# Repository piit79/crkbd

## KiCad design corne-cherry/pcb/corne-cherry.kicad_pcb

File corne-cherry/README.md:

# Corne Cherry

This version is for standard Cherry MX-compatible switches. It has specific PCBs for left and right half.

The following modifications have been made by 42. Keebs:

* Add power switch and battery contacts
* Add back the possibility to break off the 6th column
* Remove the PCB panel frame to save material/reduce waste

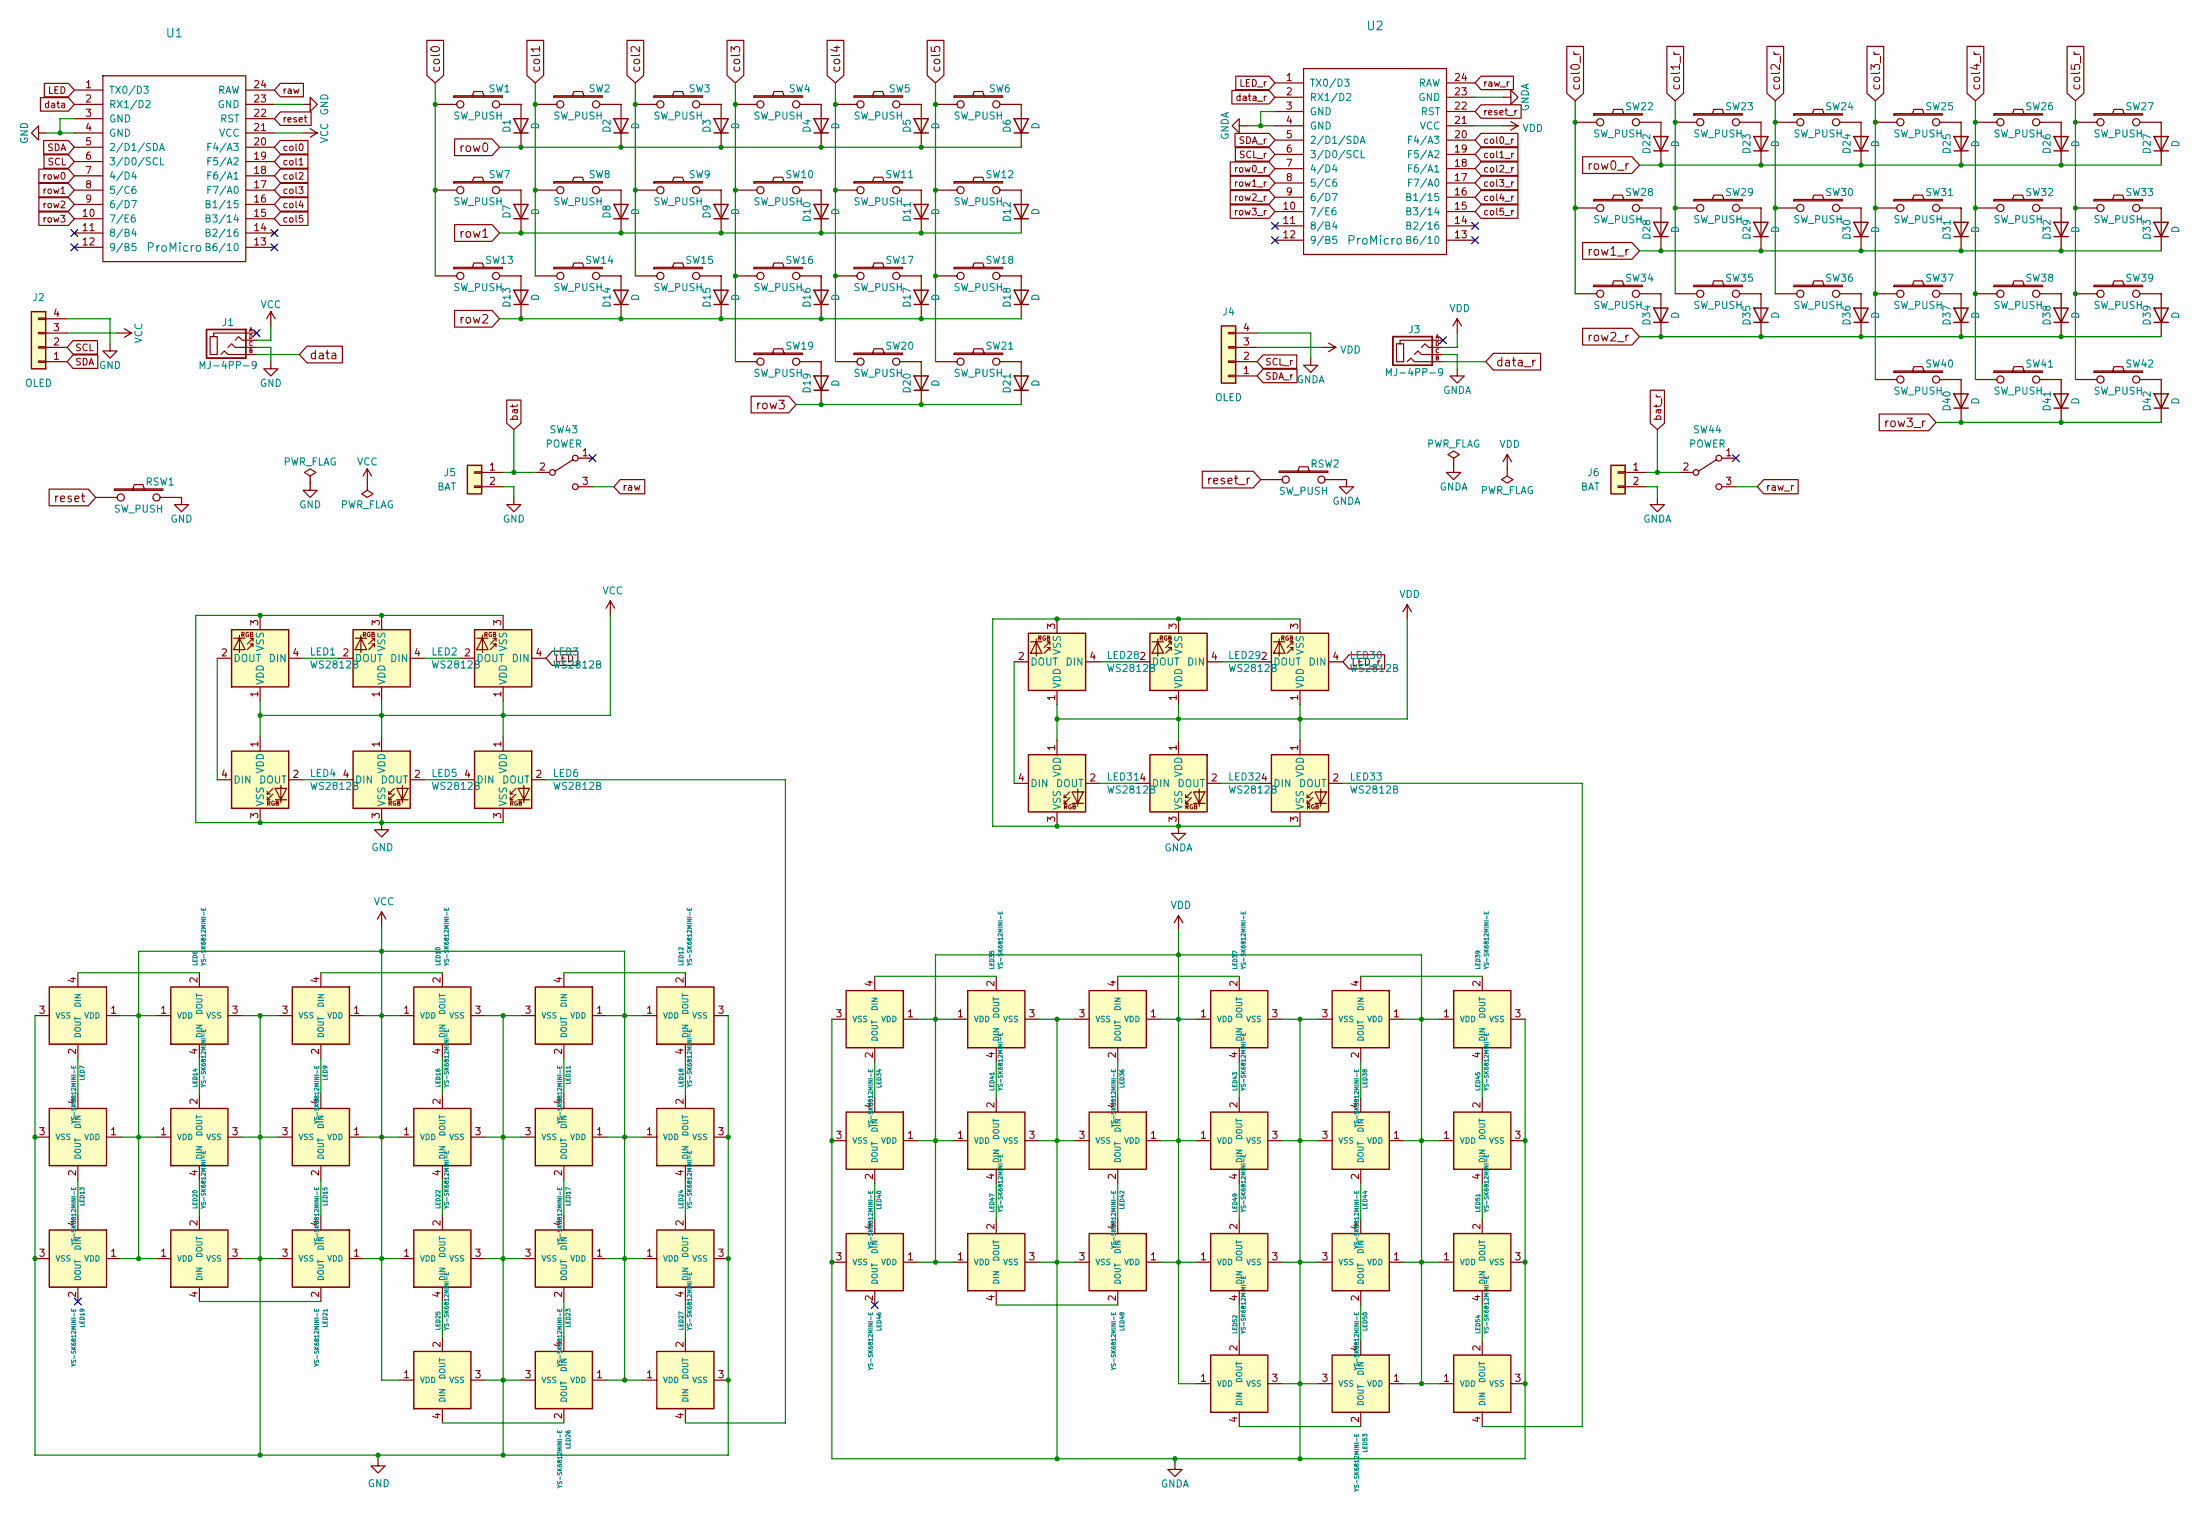
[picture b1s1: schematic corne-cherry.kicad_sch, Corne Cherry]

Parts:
D1, D2, D3, D4, D5, D6, D7, D8, D9, D10, D11, D12, D13, D14, D15, D16, D17, D18, D19, D20, D21, D22, D23, D24, D25, D26, D27, D28, D29, D30, D31, D32, D33, D34, D35, D36, D37, D38, D39, D40, D41, D42: D; D3_SMD_v2
J1, J3: MJ-4PP-9; MJ-4PP-9_1side
J2, J4: OLED; OLED_1side
J5, J6: BAT; ProMicro_Battery_Connector
LED1, LED2, LED3, LED4, LED5, LED6, LED28, LED29, LED30, LED31, LED32, LED33: WS2812B; LED_WS2812B_PLCC4_5.0x5.0mm_P3.2mm
LED7, LED8, LED9, LED10, LED11, LED12, LED13, LED14, LED15, LED16, LED17, LED18, LED19, LED20, LED21, LED22, LED23, LED24, LED25, LED26, LED27, LED34, LED35, LED36, LED37, LED38, LED39, LED40, LED41, LED42, LED43, LED44, LED45, LED46, LED47, LED48, LED49, LED50, LED51, LED52, LED53, LED54: YS-SK6812MINI-E
RSW1, RSW2: SW_PUSH; ResetSW_1side
SW1, SW2, SW3, SW4, SW5, SW6, SW7, SW8, SW9, SW10, SW11, SW12, SW13, SW14, SW15, SW16, SW17, SW18, SW19, SW20, SW22, SW23, SW24, SW25, SW26, SW27, SW28, SW29, SW30, SW31, SW32, SW33, SW34, SW35, SW36, SW37, SW38, SW39, SW40, SW41: SW_PUSH; CherryMX_Hotswap
SW21, SW42: SW_PUSH; CherryMX_Hotswap_1.5u
SW43, SW44: POWER; SW_SPDT_PCM12
U1, U2: ProMicro; ProMicro_v3

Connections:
GND: J1.C, J2.4, J5.2, LED1.3 (VSS), LED2.3 (VSS), LED3.3 (VSS), LED4.3 (VSS), LED5.3 (VSS), LED6.3 (VSS), LED7.3 (VSS), LED8.3 (VSS), LED9.3 (VSS), LED10.3 (VSS), LED11.3 (VSS), LED12.3 (VSS), LED13.3 (VSS), LED14.3 (VSS), LED15.3 (VSS), LED16.3 (VSS), LED17.3 (VSS), LED18.3 (VSS), LED19.3 (VSS), LED20.3 (VSS), LED21.3 (VSS), LED22.3 (VSS), LED23.3 (VSS), LED24.3 (VSS), LED25.3 (VSS), LED26.3 (VSS), LED27.3 (VSS), RSW1.2, U1.3 (GND), U1.4 (GND), U1.23 (GND)
GNDA: J3.C, J4.4, J6.2, LED28.3 (VSS), LED29.3 (VSS), LED30.3 (VSS), LED31.3 (VSS), LED32.3 (VSS), LED33.3 (VSS), LED34.3 (VSS), LED35.3 (VSS), LED36.3 (VSS), LED37.3 (VSS), LED38.3 (VSS), LED39.3 (VSS), LED40.3 (VSS), LED41.3 (VSS), LED42.3 (VSS), LED43.3 (VSS), LED44.3 (VSS), LED45.3 (VSS), LED46.3 (VSS), LED47.3 (VSS), LED48.3 (VSS), LED49.3 (VSS), LED50.3 (VSS), LED51.3 (VSS), LED52.3 (VSS), LED53.3 (VSS), LED54.3 (VSS), RSW2.2, U2.3 (GND), U2.4 (GND), U2.23 (GND)
LED: LED3.4 (DIN), U1.1 (TX0/D3)
LED_r: LED30.4 (DIN), U2.1 (TX0/D3)
unnamed: D1.2 (A), SW1.2
unnamed: D2.2 (A), SW2.2
unnamed: D3.2 (A), SW3.2
unnamed: D4.2 (A), SW4.2
unnamed: D5.2 (A), SW5.2
unnamed: D6.2 (A), SW6.2
unnamed: D7.2 (A), SW7.2
unnamed: D8.2 (A), SW8.2
unnamed: D9.2 (A), SW9.2
unnamed: D10.2 (A), SW10.2
unnamed: D11.2 (A), SW11.2
unnamed: D12.2 (A), SW12.2
unnamed: D13.2 (A), SW13.2
unnamed: D14.2 (A), SW14.2
unnamed: D15.2 (A), SW15.2
unnamed: D16.2 (A), SW16.2
unnamed: D17.2 (A), SW17.2
unnamed: D18.2 (A), SW18.2
unnamed: D19.2 (A), SW19.2
unnamed: D20.2 (A), SW20.2
unnamed: D21.2 (A), SW21.2
unnamed: D22.2 (A), SW22.2
unnamed: D23.2 (A), SW23.2
unnamed: D24.2 (A), SW24.2
unnamed: D25.2 (A), SW25.2
unnamed: D26.2 (A), SW26.2
unnamed: D27.2 (A), SW27.2
unnamed: D28.2 (A), SW28.2
unnamed: D29.2 (A), SW29.2
unnamed: D30.2 (A), SW30.2
unnamed: D31.2 (A), SW31.2
unnamed: D32.2 (A), SW32.2
unnamed: D33.2 (A), SW33.2
unnamed: D34.2 (A), SW34.2
unnamed: D35.2 (A), SW35.2
unnamed: D36.2 (A), SW36.2
unnamed: D37.2 (A), SW37.2
unnamed: D38.2 (A), SW38.2
unnamed: D39.2 (A), SW39.2
unnamed: D40.2 (A), SW40.2
unnamed: D41.2 (A), SW41.2
unnamed: D42.2 (A), SW42.2
unnamed: LED1.2 (DOUT), LED4.4 (DIN)
unnamed: LED1.4 (DIN), LED2.2 (DOUT)
unnamed: LED2.4 (DIN), LED3.2 (DOUT)
unnamed: LED4.2 (DOUT), LED5.4 (DIN)
unnamed: LED5.2 (DOUT), LED6.4 (DIN)
unnamed: LED7.4 (DIN), LED8.2 (DOUT)
unnamed: LED9.4 (DIN), LED10.2 (DOUT)
unnamed: LED10.4 (DIN), LED16.2 (DOUT)
unnamed: LED11.2 (DOUT), LED17.4 (DIN)
unnamed: LED11.4 (DIN), LED12.2 (DOUT)
unnamed: LED12.4 (DIN), LED18.2 (DOUT)
unnamed: LED13.2 (DOUT), LED19.4 (DIN)
unnamed: LED7.2 (DOUT), LED13.4 (DIN)
unnamed: LED8.4 (DIN), LED14.2 (DOUT)
unnamed: LED14.4 (DIN), LED20.2 (DOUT)
unnamed: LED15.2 (DOUT), LED21.4 (DIN)
unnamed: LED9.2 (DOUT), LED15.4 (DIN)
unnamed: LED16.4 (DIN), LED22.2 (DOUT)
unnamed: LED17.2 (DOUT), LED23.4 (DIN)
unnamed: LED18.4 (DIN), LED24.2 (DOUT)
unnamed: LED20.4 (DIN), LED21.2 (DOUT)
unnamed: LED22.4 (DIN), LED25.2 (DOUT)
unnamed: LED23.2 (DOUT), LED26.4 (DIN)
unnamed: LED24.4 (DIN), LED27.2 (DOUT)
unnamed: LED25.4 (DIN), LED26.2 (DOUT)
unnamed: LED6.2 (DOUT), LED27.4 (DIN)
unnamed: LED28.2 (DOUT), LED31.4 (DIN)
unnamed: LED28.4 (DIN), LED29.2 (DOUT)
unnamed: LED29.4 (DIN), LED30.2 (DOUT)
unnamed: LED31.2 (DOUT), LED32.4 (DIN)
unnamed: LED32.2 (DOUT), LED33.4 (DIN)
unnamed: LED33.2 (DOUT), LED54.4 (DIN)
unnamed: LED34.2 (DOUT), LED40.4 (DIN)
unnamed: LED34.4 (DIN), LED35.2 (DOUT)
unnamed: LED35.4 (DIN), LED41.2 (DOUT)
unnamed: LED36.2 (DOUT), LED42.4 (DIN)
unnamed: LED36.4 (DIN), LED37.2 (DOUT)
unnamed: LED37.4 (DIN), LED43.2 (DOUT)
unnamed: LED38.2 (DOUT), LED44.4 (DIN)
unnamed: LED38.4 (DIN), LED39.2 (DOUT)
unnamed: LED39.4 (DIN), LED45.2 (DOUT)
unnamed: LED40.2 (DOUT), LED46.4 (DIN)
unnamed: LED41.4 (DIN), LED47.2 (DOUT)
unnamed: LED42.2 (DOUT), LED48.4 (DIN)
unnamed: LED43.4 (DIN), LED49.2 (DOUT)
unnamed: LED44.2 (DOUT), LED50.4 (DIN)
unnamed: LED45.4 (DIN), LED51.2 (DOUT)
unnamed: LED47.4 (DIN), LED48.2 (DOUT)
unnamed: LED49.4 (DIN), LED52.2 (DOUT)
unnamed: LED50.2 (DOUT), LED53.4 (DIN)
unnamed: LED51.4 (DIN), LED54.2 (DOUT)
unnamed: LED52.4 (DIN), LED53.2 (DOUT)
SCL: J2.2, U1.6 (3/D0/SCL)
SCL_r: J4.2, U2.6 (3/D0/SCL)
SDA: J2.1, U1.5 (2/D1/SDA)
SDA_r: J4.1, U2.5 (2/D1/SDA)
VCC: J1.D, J2.3, LED1.1 (VDD), LED2.1 (VDD), LED3.1 (VDD), LED4.1 (VDD), LED5.1 (VDD), LED6.1 (VDD), LED7.1 (VDD), LED8.1 (VDD), LED9.1 (VDD), LED10.1 (VDD), LED11.1 (VDD), LED12.1 (VDD), LED13.1 (VDD), LED14.1 (VDD), LED15.1 (VDD), LED16.1 (VDD), LED17.1 (VDD), LED18.1 (VDD), LED19.1 (VDD), LED20.1 (VDD), LED21.1 (VDD), LED22.1 (VDD), LED23.1 (VDD), LED24.1 (VDD), LED25.1 (VDD), LED26.1 (VDD), LED27.1 (VDD), U1.21 (VCC)
VDD: J3.D, J4.3, LED28.1 (VDD), LED29.1 (VDD), LED30.1 (VDD), LED31.1 (VDD), LED32.1 (VDD), LED33.1 (VDD), LED34.1 (VDD), LED35.1 (VDD), LED36.1 (VDD), LED37.1 (VDD), LED38.1 (VDD), LED39.1 (VDD), LED40.1 (VDD), LED41.1 (VDD), LED42.1 (VDD), LED43.1 (VDD), LED44.1 (VDD), LED45.1 (VDD), LED46.1 (VDD), LED47.1 (VDD), LED48.1 (VDD), LED49.1 (VDD), LED50.1 (VDD), LED51.1 (VDD), LED52.1 (VDD), LED53.1 (VDD), LED54.1 (VDD), U2.21 (VCC)
bat: J5.1, SW43.2 (B)
bat_r: J6.1, SW44.2 (B)
col0: SW1.1, SW7.1, SW13.1, U1.20 (F4/A3)
col0_r: SW22.1, SW28.1, SW34.1, U2.20 (F4/A3)
col1: SW2.1, SW8.1, SW14.1, U1.19 (F5/A2)
col1_r: SW23.1, SW29.1, SW35.1, U2.19 (F5/A2)
col2: SW3.1, SW9.1, SW15.1, U1.18 (F6/A1)
col2_r: SW24.1, SW30.1, SW36.1, U2.18 (F6/A1)
col3: SW4.1, SW10.1, SW16.1, SW19.1, U1.17 (F7/A0)
col3_r: SW25.1, SW31.1, SW37.1, SW40.1, U2.17 (F7/A0)
col4: SW5.1, SW11.1, SW17.1, SW20.1, U1.16 (B1/15)
col4_r: SW26.1, SW32.1, SW38.1, SW41.1, U2.16 (B1/15)
col5: SW6.1, SW12.1, SW18.1, SW21.1, U1.15 (B3/14)
col5_r: SW27.1, SW33.1, SW39.1, SW42.1, U2.15 (B3/14)
data: J1.B, U1.2 (RX1/D2)
data_r: J3.B, U2.2 (RX1/D2)
raw: SW43.3 (C), U1.24 (RAW)
raw_r: SW44.3 (C), U2.24 (RAW)
reset: RSW1.1, U1.22 (RST)
reset_r: RSW2.1, U2.22 (RST)
row0: D1.1 (K), D2.1 (K), D3.1 (K), D4.1 (K), D5.1 (K), D6.1 (K), U1.7 (4/D4)
row0_r: D22.1 (K), D23.1 (K), D24.1 (K), D25.1 (K), D26.1 (K), D27.1 (K), U2.7 (4/D4)
row1: D7.1 (K), D8.1 (K), D9.1 (K), D10.1 (K), D11.1 (K), D12.1 (K), U1.8 (5/C6)
row1_r: D28.1 (K), D29.1 (K), D30.1 (K), D31.1 (K), D32.1 (K), D33.1 (K), U2.8 (5/C6)
row2: D13.1 (K), D14.1 (K), D15.1 (K), D16.1 (K), D17.1 (K), D18.1 (K), U1.9 (6/D7)
row2_r: D34.1 (K), D35.1 (K), D36.1 (K), D37.1 (K), D38.1 (K), D39.1 (K), U2.9 (6/D7)
row3: D19.1 (K), D20.1 (K), D21.1 (K), U1.10 (7/E6)
row3_r: D40.1 (K), D41.1 (K), D42.1 (K), U2.10 (7/E6)

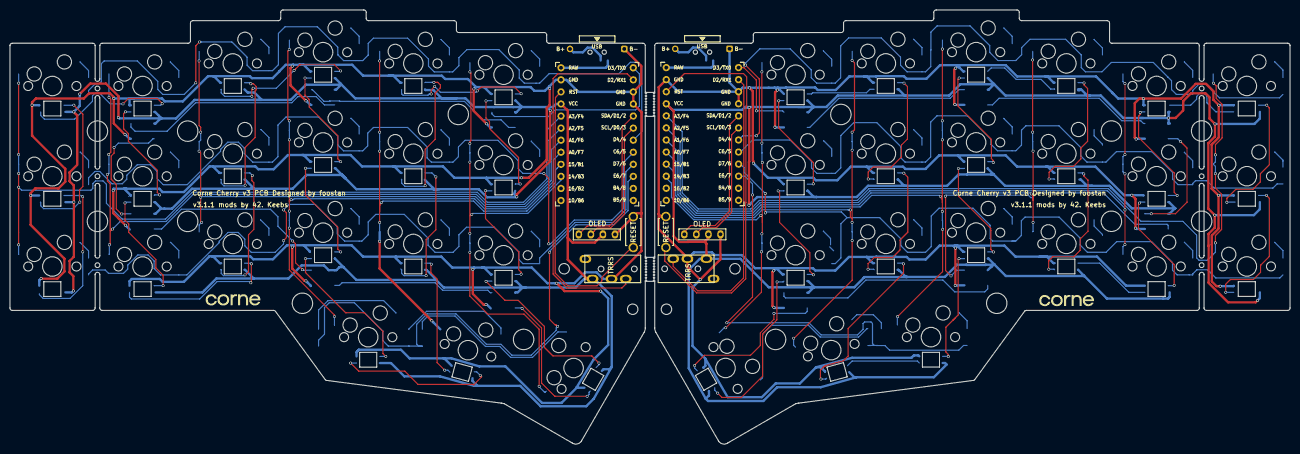
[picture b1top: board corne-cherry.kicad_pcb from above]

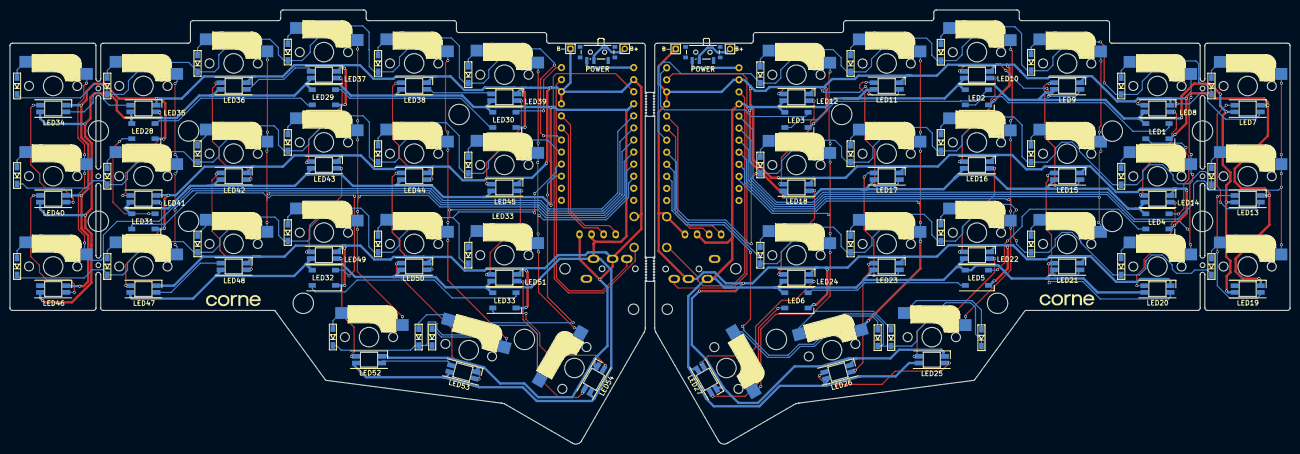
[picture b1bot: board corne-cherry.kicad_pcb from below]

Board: 2 copper layers, 269.5 x 91.4 mm, 168 parts (102 on the bottom side), 132 nets.

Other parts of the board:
Ref**: Val**; M2_HOLE_v2
Ref**#2, Ref**#3, Ref**#4, Ref**#5, Ref**#6, Ref**#7, Ref**#8, Ref**#9, Ref**#10, Ref**#11, Ref**#12, Ref**#13, Ref**#14, Ref**#15, Ref**#16, Ref**#17, Ref**#18: Val**; M2_HOLE_v2

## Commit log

2022-10-27 Add local footprint library with an under-Pro Micro battery connector
2023-02-06 Corne Cherry: Add power switches and battery connectors at the top of Pro Micro footprints
    Also fix all board edge issues
2023-03-25 Remove the PCB frame to save material; more edge fixes and silkscreen updates
2023-11-13 Add the possibility to break off the 6th column
